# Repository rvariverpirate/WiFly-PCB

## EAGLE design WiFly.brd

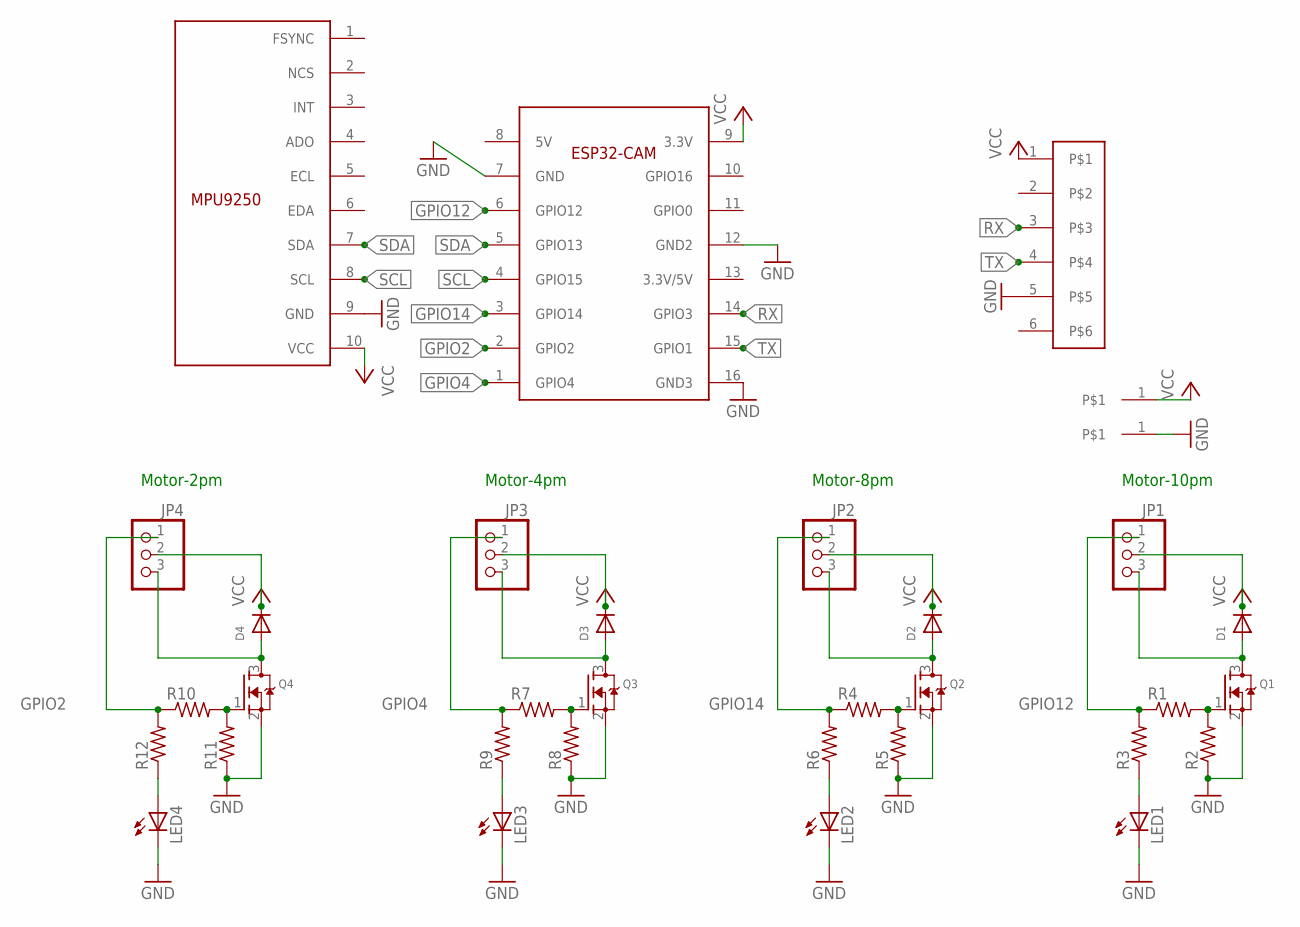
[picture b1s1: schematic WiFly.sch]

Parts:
+: 22AWG22AWG-MALE; HDRV1W64P0_1X1_193X193X447B
-: 22AWG22AWG-MALE; HDRV1W64P0_1X1_193X193X447B
D1, D2, D3, D4: DIODESOD-323F; SOD-323F
JP1, JP2, JP3, JP4: PINHD-1X3CB; 1X03-CLEANBIG
LED1, LED2, LED3, LED4: LEDCHIP-LED0603; CHIP-LED0603
Q1, Q2, Q3, Q4: MOSFET-NREFLOW; SOT23
R1, R2, R3, R4, R5, R6, R7, R8, R9, R10, R11, R12: R-US_R0603; R0603
U$1: MPU9250FEMALE_HEADER; HDRVR10W64P254_1X10_2540X254X254B
U$2: ESP32-CAMESP32-CAM; HDRVR16W64P2286X254_2X8_2032X2540X254B
U$3: 6-PINFEMALE-6-PIN-A; HDRVR6W64P254_1X6_1524X254X762B

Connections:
GND: -.1, LED1.C, LED2.C, LED3.C, LED4.C, Q1.2 (S), Q2.2 (S), Q3.2 (S), Q4.2 (S), R2.1, R5.1, R8.1, R11.1, U$1.9 (GND), U$2.7 (GND), U$2.12 (GND2), U$2.16 (GND3), U$3.5
GPIO2: JP4.1, R10.1, R12.2, U$2.2 (GPIO2)
GPIO4: JP3.1, R7.1, R9.2, U$2.1 (GPIO4)
GPIO12: JP1.1, R1.1, R3.2, U$2.6 (GPIO12)
GPIO14: JP2.1, R4.1, R6.2, U$2.3 (GPIO14)
unnamed: D1.A, JP1.3, Q1.3 (D)
unnamed: Q1.1 (G), R1.2, R2.2
unnamed: LED1.A, R3.1
unnamed: Q2.1 (G), R4.2, R5.2
unnamed: LED2.A, R6.1
unnamed: D2.A, JP2.3, Q2.3 (D)
unnamed: Q3.1 (G), R7.2, R8.2
unnamed: LED3.A, R9.1
unnamed: D3.A, JP3.3, Q3.3 (D)
unnamed: Q4.1 (G), R10.2, R11.2
unnamed: LED4.A, R12.1
unnamed: D4.A, JP4.3, Q4.3 (D)
RX: U$2.14 (GPIO3), U$3.3
SCL: U$1.8 (SCL), U$2.4 (GPIO15)
SDA: U$1.7 (SDA), U$2.5 (GPIO13)
TX: U$2.15 (GPIO1), U$3.4
VCC: +.1, D1.C, D2.C, D3.C, D4.C, JP1.2, JP2.2, JP3.2, JP4.2, U$1.10 (VCC), U$2.9 (3.3V), U$3.1

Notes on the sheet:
Motor-10pm
Motor-8pm
Motor-4pm
Motor-2pm

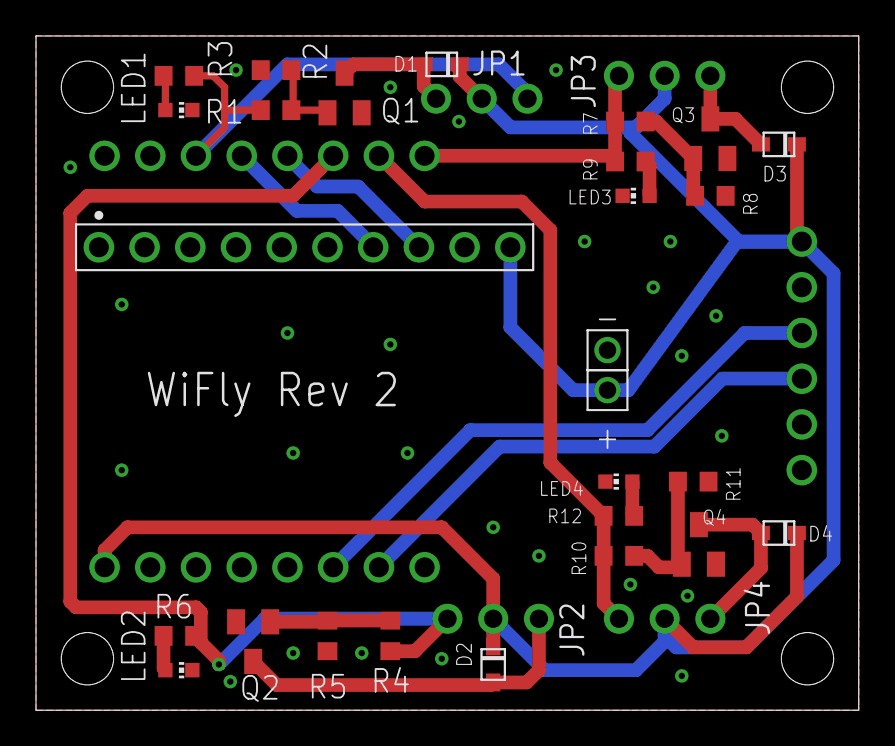
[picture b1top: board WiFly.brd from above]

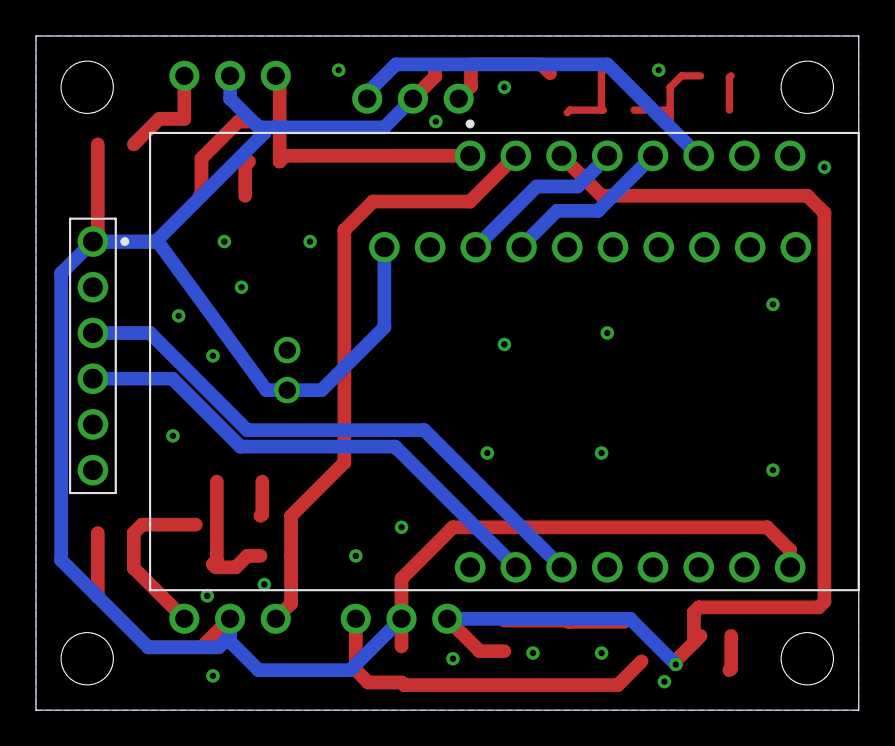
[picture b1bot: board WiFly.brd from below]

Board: 2 copper layers, 45.7 x 37.5 mm, 33 parts (2 on the bottom side), 22 nets.

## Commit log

2021-02-17 Initial commit of WiFly PCB
2021-02-19 I honestly forgot what I updated
2021-03-01 Flipped ESP32CAM for physical layout, reworking other layouts
2021-03-01 Added mounting holes 9AWG 0.1144 in
2021-03-01 Initial routing, need to re-assign Motor Driver IO pins
2021-03-02 Routed remaining wires and polygon pour, no errors ERC detected
2021-03-06 Widened board a bit to provide clearance for mounting screws. Rev 1 FingersCrossed
2021-04-18 Fix ESP32 layout and slide location down
2021-04-19 Make compatible with lower power battery connection
2021-05-08 Rev2 and 3D ILF export
2021-05-10 Added WiFly body for SolidWorks
2021-05-23 Added custom component library files
